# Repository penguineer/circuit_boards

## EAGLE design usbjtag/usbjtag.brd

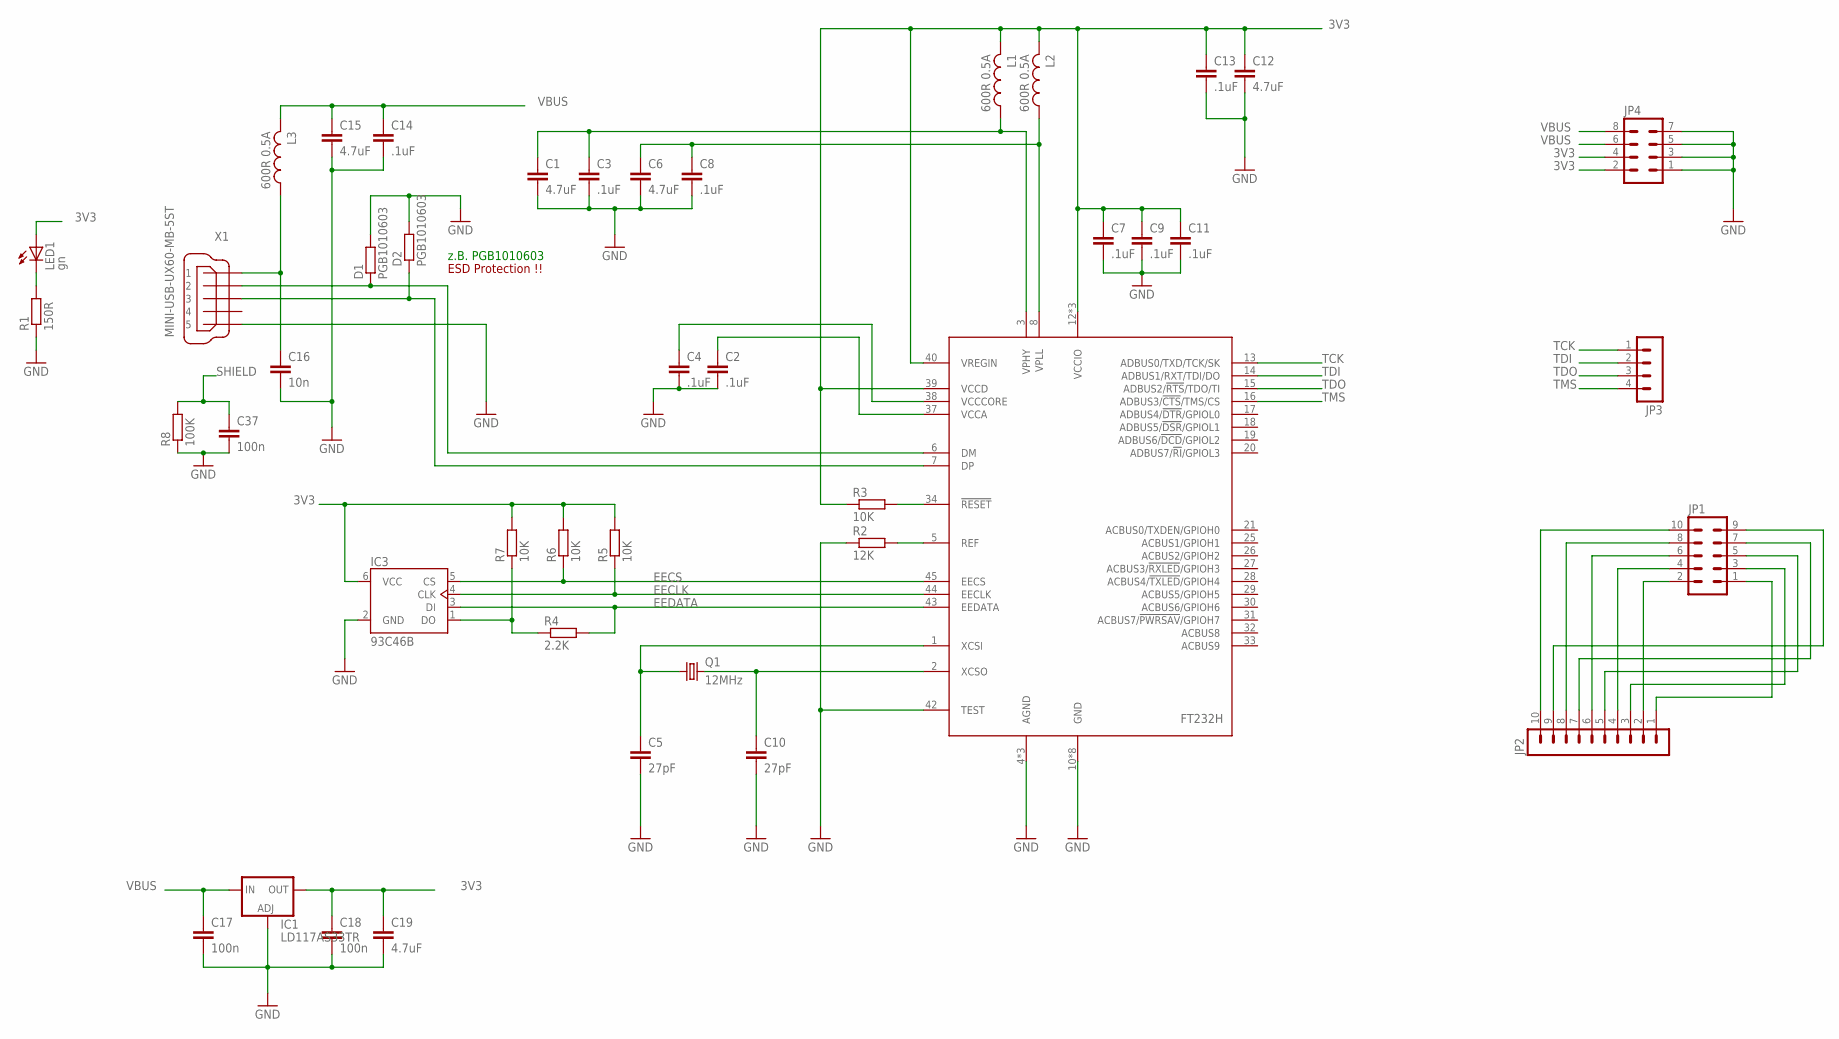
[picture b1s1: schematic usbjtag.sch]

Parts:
C1, C6, C12, C15, C19: 4.7uF; C0805
C2, C3, C4, C7, C8, C9, C11, C13, C14: .1uF; C0805
C5, C10: 27pF; C0805
C16: 10n; C0805
C17, C18, C37: 100n; C0805
D1, D2: PGB1010603; R0603
IC1: LD117AS33TR; SOT223
IC2: FT232H; LQFP48
IC3: 93C46B; SOT23-6
JP1: MA05-2
JP2: MA10-1
JP3: MA04-1
JP4: MA04-2
L1, L2, L3: 600R 0.5A; L4532M
LED1: gn; CHIPLED_0805
Q1: 12MHz; CRYSTAL3.2X2.5MM
R1: 150R; R0805
R2: 12K; R0805
R3, R5, R6, R7: 10K; R0805
R4: 2.2K; R0805
R8: 100K; R0805
X1: MINI-USB-UX60-MB-5ST; UX60-MB-5ST

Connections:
3V3: C7.1, C9.1, C11.1, C12.1, C13.1, C18.1, C19.1, IC1.4 (OUT), IC2.12 (VCCIO), IC2.24 (VCCIO), IC2.39 (VCCD), IC2.40 (VREGIN), IC2.46 (VCCIO), IC3.6 (VCC), JP4.2, JP4.4, L1.2, L2.2, LED1.A, R3.1, R5.2, R6.2, R7.2
EECLK: IC2.44 (EECLK), IC3.4 (CLK), R5.1
EECS: IC2.45 (EECS), IC3.5 (CS), R6.1
EEDATA: IC2.43 (EEDATA), IC3.3 (DI), R4.2
GND: C1.2, C2.2, C3.2, C4.2, C5.2, C6.2, C7.2, C8.2, C9.2, C10.2, C11.2, C12.2, C13.2, C14.2, C15.2, C16.2, C17.2, C18.2, C19.2, C37.2, D1.2, D2.2, IC1.1 (ADJ), IC2.4 (AGND), IC2.9 (AGND), IC2.10 (GND), IC2.11 (GND), IC2.22 (GND), IC2.23 (GND), IC2.35 (GND), IC2.36 (GND), IC2.41 (AGND), IC2.42 (TEST), IC2.47 (GND), IC2.48 (GND), IC3.2 (GND), JP4.1, JP4.3, JP4.5, JP4.7, R1.1, R2.1, R8.1, X1.5
unnamed: IC3.1 (DO), R4.1, R7.1
unnamed: IC2.34 (!RESET), R3.2
unnamed: IC2.5 (REF), R2.2
unnamed: LED1.C, R1.2
unnamed: D2.1, IC2.7 (DP), X1.3
unnamed: C10.1, IC2.2 (XCSO), Q1.3 (2)
unnamed: C5.1, IC2.1 (XCSI), Q1.1
unnamed: C2.1, IC2.37 (VCCA)
unnamed: JP1.1, JP2.1
unnamed: JP1.2, JP2.2
unnamed: JP1.3, JP2.3
unnamed: JP1.4, JP2.4
unnamed: JP1.5, JP2.5
unnamed: JP1.6, JP2.6
unnamed: JP1.7, JP2.7
unnamed: JP1.8, JP2.8
unnamed: JP1.10, JP2.10
unnamed: JP1.9, JP2.9
unnamed: D1.1, IC2.6 (DM), X1.2
SHIELD: C37.1, R8.2
TCK: IC2.13 (ADBUS0/TXD/TCK/SK), JP3.1
TDI: IC2.14 (ADBUS1/RXT/TDI/DO), JP3.2
TDO: IC2.15 (ADBUS2/!RTS!/TDO/TI), JP3.3
TMS: IC2.16 (ADBUS3/!CTS!/TMS/CS), JP3.4
VBUS: C14.1, C15.1, C17.1, IC1.3 (IN), JP4.6, JP4.8, L3.2
VCORE: C4.1, IC2.38 (VCCCORE)
VPHY: C1.1, C3.1, IC2.3 (VPHY), L1.1
VPLL: C6.1, C8.1, IC2.8 (VPLL), L2.1
VUSB: C16.1, L3.1, X1.1

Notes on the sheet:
ESD Protection !!
z.B. PGB1010603

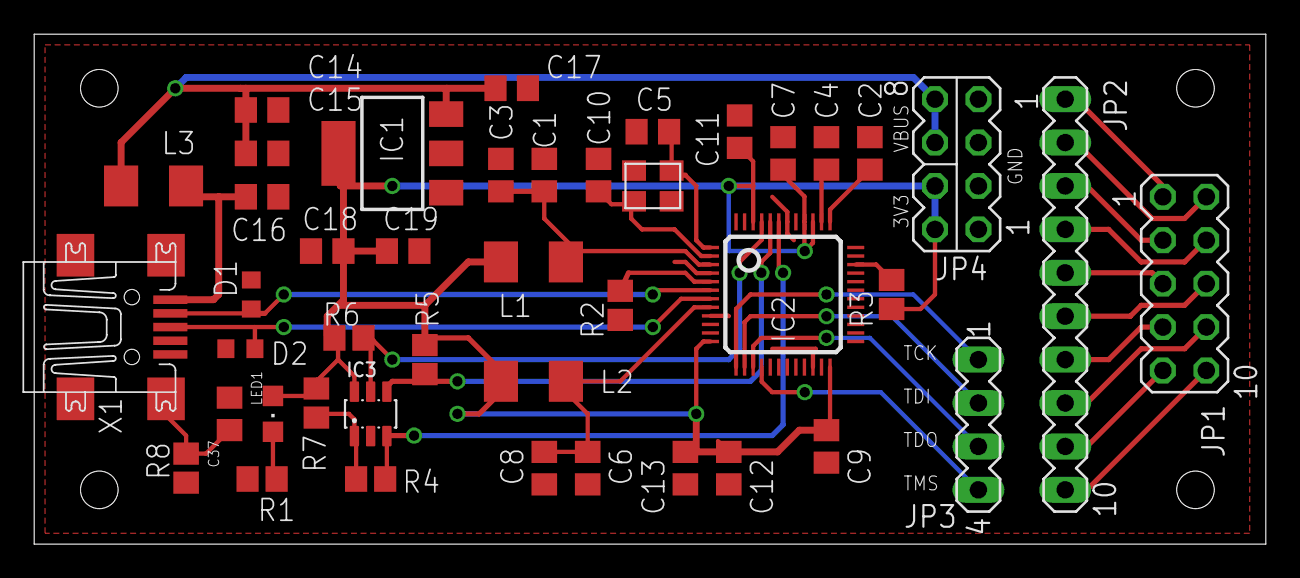
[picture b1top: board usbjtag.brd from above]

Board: 2 copper layers, 72.1 x 29.8 mm, 43 parts (0 on the bottom side), 34 nets.

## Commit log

2015-12-06 USB JTAG: Schematics and Board
2015-12-06 USB JTAG: BOM
2015-12-06 USB JTAG: License

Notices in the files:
usbjtag/usbjtag.brd:
CC-BY-SA Netz39 e.V.
